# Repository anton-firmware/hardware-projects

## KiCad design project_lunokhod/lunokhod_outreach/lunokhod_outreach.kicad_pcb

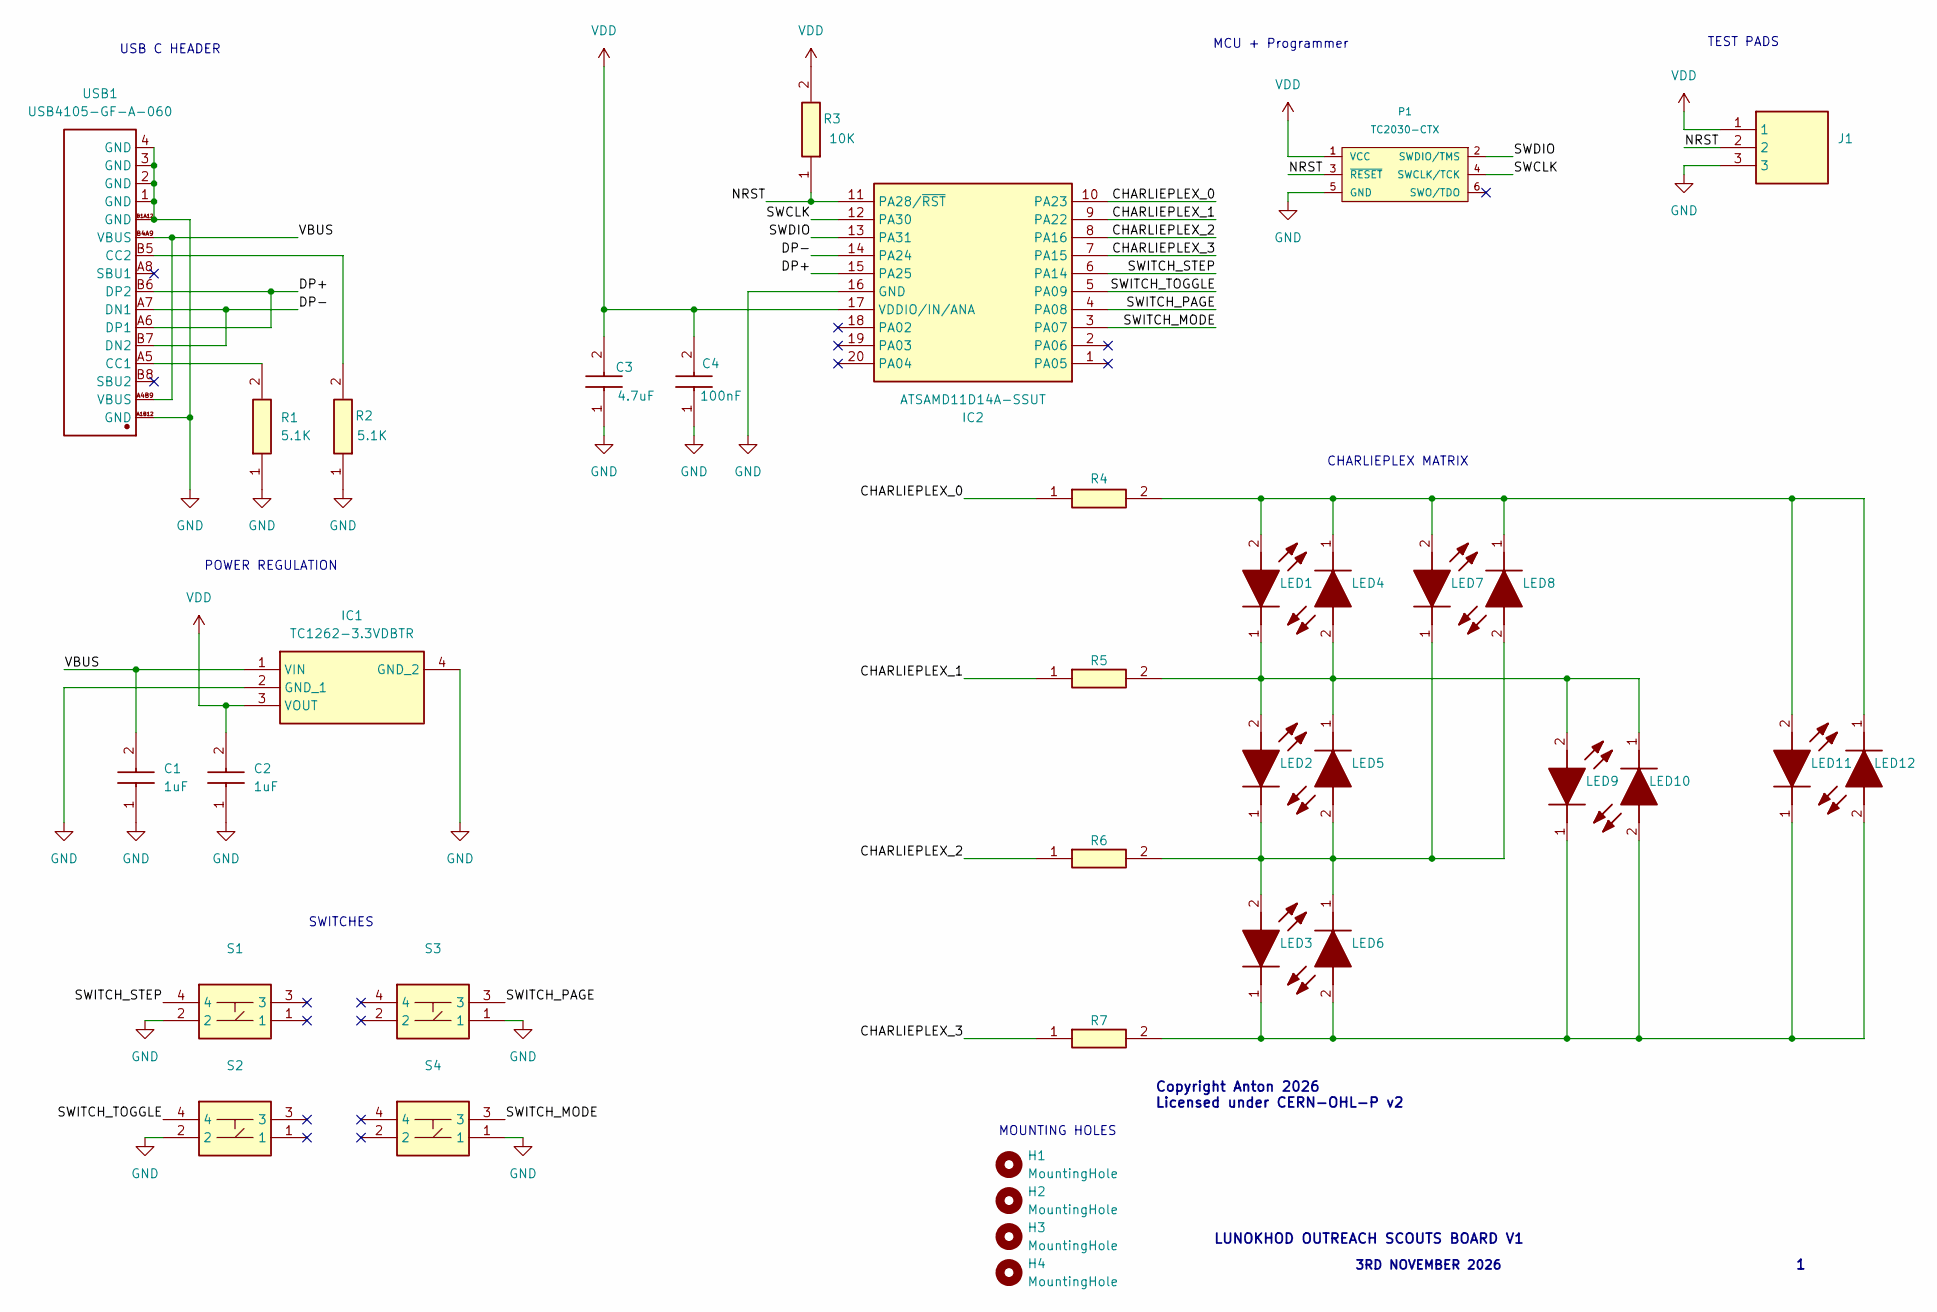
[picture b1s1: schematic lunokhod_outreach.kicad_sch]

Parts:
C1, C2: 1uF; C0603; Manufacturer_Part_Number C0603C101K5RACAUTO7411
C3: 4.7uF; C0603; Manufacturer_Part_Number C0603C101K5RACAUTO7411
C4: 100nF; C0603; Manufacturer_Part_Number C0603C101K5RACAUTO7411
H1, H2, H3, H4: MountingHole; MountingHole_2.5mm
IC1: TC1262-3.3VDBTR; SOT230P700X180-4N; Manufacturer_Part_Number TC1262-3.3VDBTR
IC2: ATSAMD11D14A-SSUT; SOIC127P1032X265-20N; Manufacturer_Part_Number ATSAMD11D14A-SSUT
J1: 0022285034; Manufacturer_Part_Number 0022285034
LED1, LED2, LED3, LED4, LED5, LED6, LED7, LED8, LED9, LED10, LED11, LED12: 703-0100; 7030100; Manufacturer_Part_Number 703-0100
P1: TC2030-CTX; TC2030_SMALL
R1, R2: 5.1K; ERJPC3D9763V; Manufacturer_Part_Number ERJ-PC3B4702V
R3: 10K; ERJPC3D9763V; Manufacturer_Part_Number ERJ-PC3B4702V
R4, R5, R6: LibraryLoader:RESAD3800W75L1600D550; ERJPC3D9763V; Manufacturer_Part_Number MCKNP02WJ0102A19
R7: MCKNP02WJ0102A19; ERJPC3D9763V; Manufacturer_Part_Number MCKNP02WJ0102A19
S1, S2, S3, S4: B3F-1020; B3F1000; Manufacturer_Part_Number B3F-1020
USB1: USB4105-GF-A-060; USB-C-SMD_GT-USB-7010E-1; Manufacturer Part USB4105-GF-A-060

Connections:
/CHARLIEPLEX_0: IC2.10 (PA23), R4.1
/CHARLIEPLEX_1: IC2.9 (PA22), R5.1
/CHARLIEPLEX_2: IC2.8 (PA16), R6.1
/CHARLIEPLEX_3: IC2.7 (PA15), R7.1
/DP+: IC2.15 (PA25), USB1.A6 (DP1), USB1.B6 (DP2)
/DP-: IC2.14 (PA24), USB1.A7 (DN1), USB1.B7 (DN2)
/NRST: IC2.11 (PA28/~RST), J1.2, P1.3 (~RESET), R3.1
/SWCLK: IC2.12 (PA30), P1.4 (SWCLK/TCK)
/SWDIO: IC2.13 (PA31), P1.2 (SWDIO/TMS)
/SWITCH_MODE: IC2.3 (PA07), S4.3
/SWITCH_PAGE: IC2.4 (PA08), S3.3
/SWITCH_STEP: IC2.6 (PA14), S1.4
/SWITCH_TOGGLE: IC2.5 (PA09), S2.4
/VBUS: C1.2, IC1.1 (VIN), USB1.A4B9 (VBUS), USB1.B4A9 (VBUS)
GND: C1.1, C2.1, C3.1, C4.1, IC1.2 (GND_1), IC1.4 (GND_2), IC2.16 (GND), J1.3, P1.5 (GND), R1.1, R2.1, S1.2, S2.2, S3.1, S4.1, USB1.1 (GND), USB1.2 (GND), USB1.3 (GND), USB1.4 (GND), USB1.A1B12 (GND), USB1.B1A12 (GND)
unnamed: LED1.2 (A), LED4.1 (K), LED7.2 (A), LED8.1 (K), LED11.2 (A), LED12.1 (K), R4.2
unnamed: LED1.1 (K), LED2.2 (A), LED4.2 (A), LED5.1 (K), LED9.2 (A), LED10.1 (K), R5.2
unnamed: LED2.1 (K), LED3.2 (A), LED5.2 (A), LED6.1 (K), LED7.1 (K), LED8.2 (A), R6.2
unnamed: LED3.1 (K), LED6.2 (A), LED9.1 (K), LED10.2 (A), LED11.1 (K), LED12.2 (A), R7.2
unnamed: R1.2, USB1.A5 (CC1)
unnamed: R2.2, USB1.B5 (CC2)
VDD: C2.2, C3.2, C4.2, IC1.3 (VOUT), IC2.17 (VDDIO/IN/ANA), J1.1, P1.1 (VCC), R3.2

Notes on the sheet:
SWITCHES
LUNOKHOD OUTREACH SCOUTS BOARD V1
POWER REGULATION
CHARLIEPLEX MATRIX
TEST PADS
Copyright Anton 2026 Licensed under CERN-OHL-P v2
USB C HEADER
MCU + Programmer
MOUNTING HOLES
3RD NOVEMBER 2026

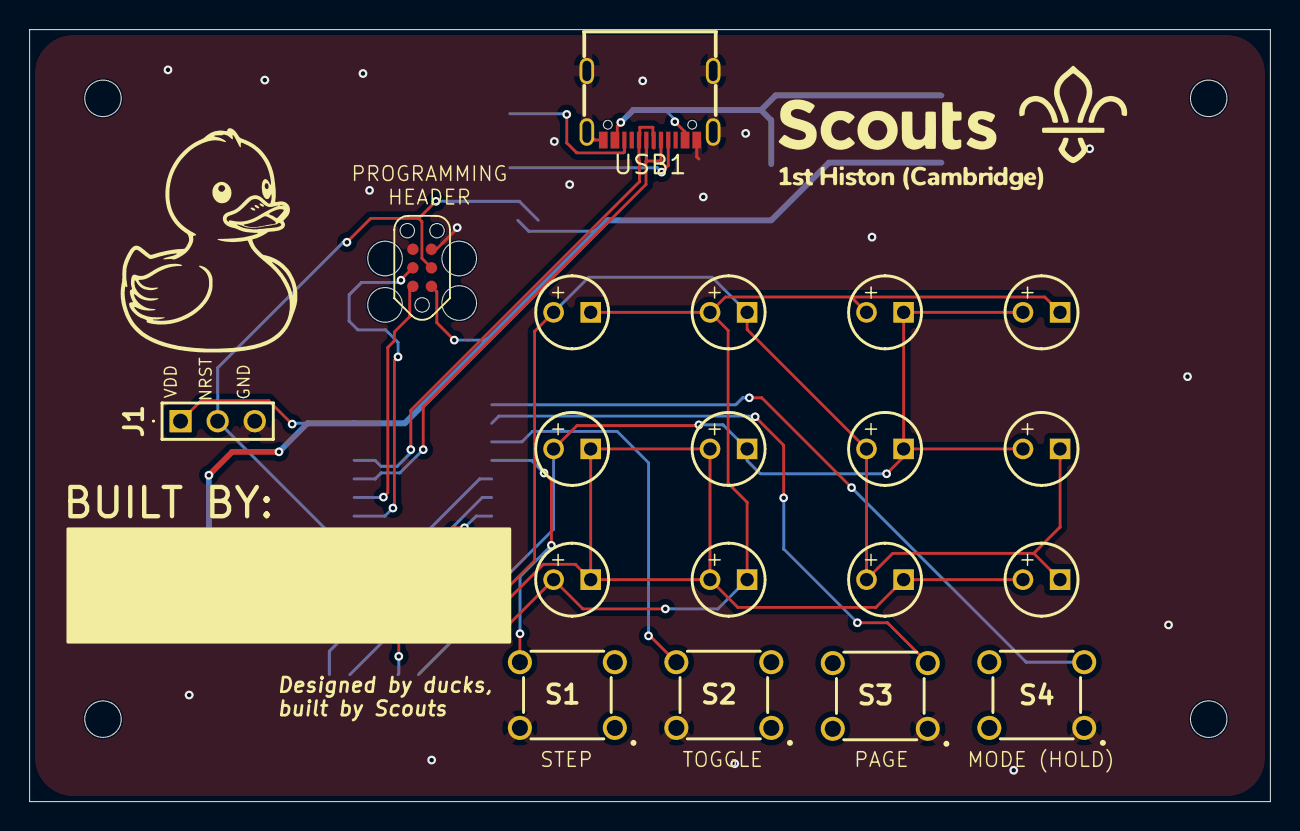
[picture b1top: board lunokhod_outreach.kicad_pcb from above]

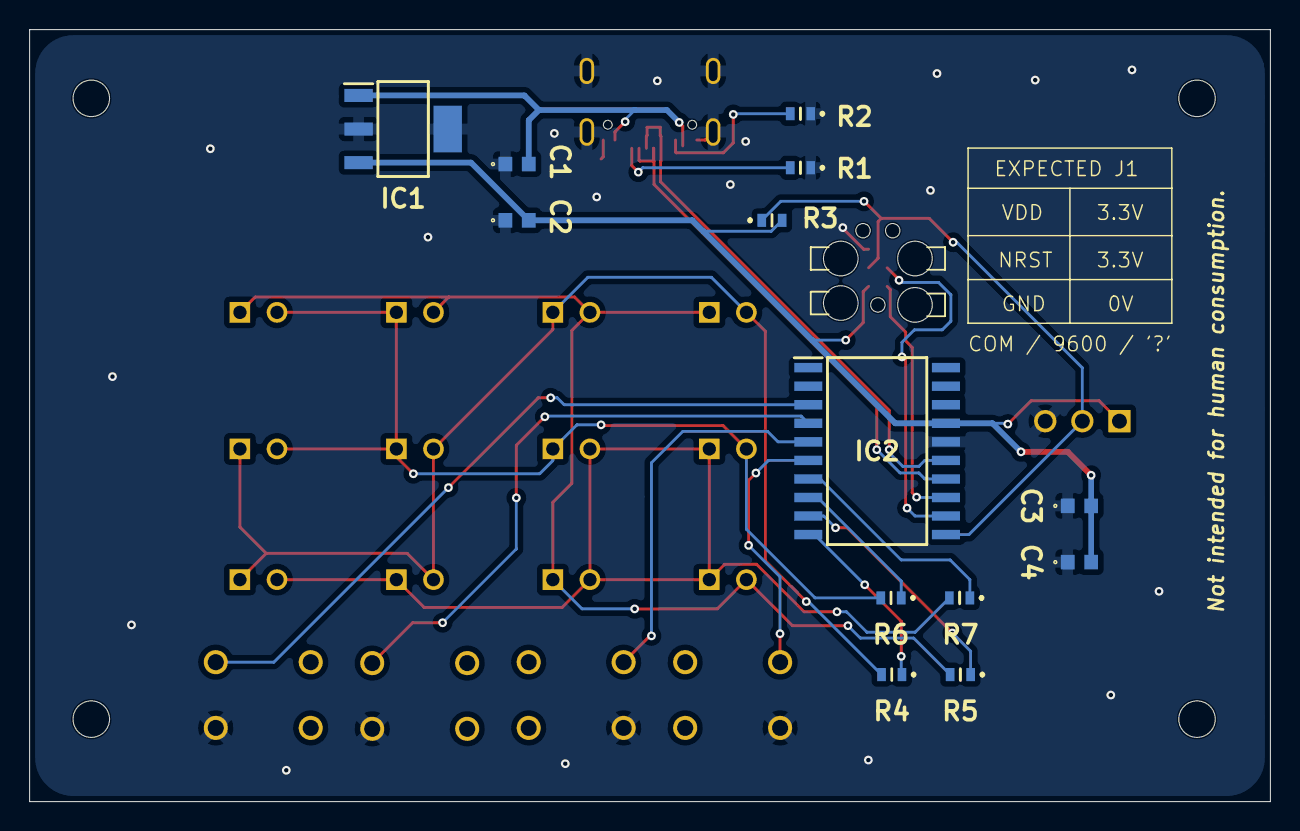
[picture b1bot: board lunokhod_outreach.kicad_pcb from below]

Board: 2 copper layers, 84.9 x 52.9 mm, 36 parts (13 on the bottom side), 22 nets.

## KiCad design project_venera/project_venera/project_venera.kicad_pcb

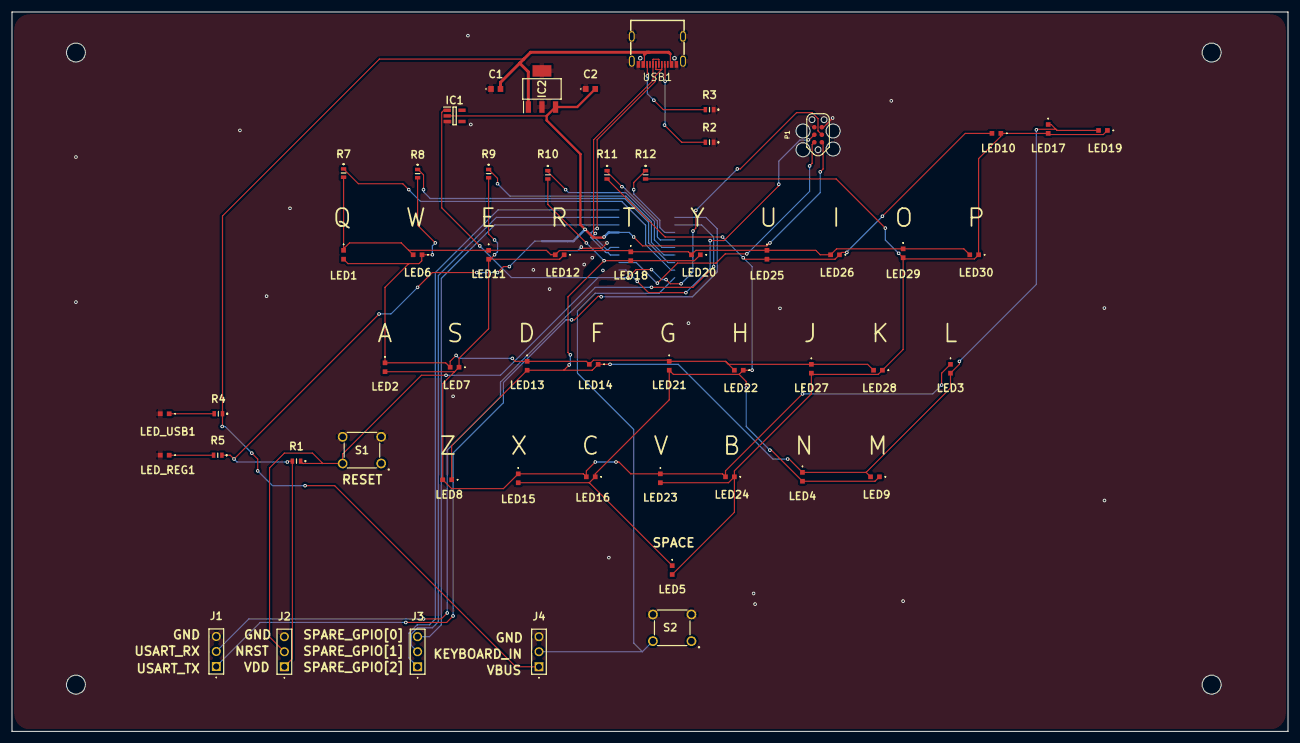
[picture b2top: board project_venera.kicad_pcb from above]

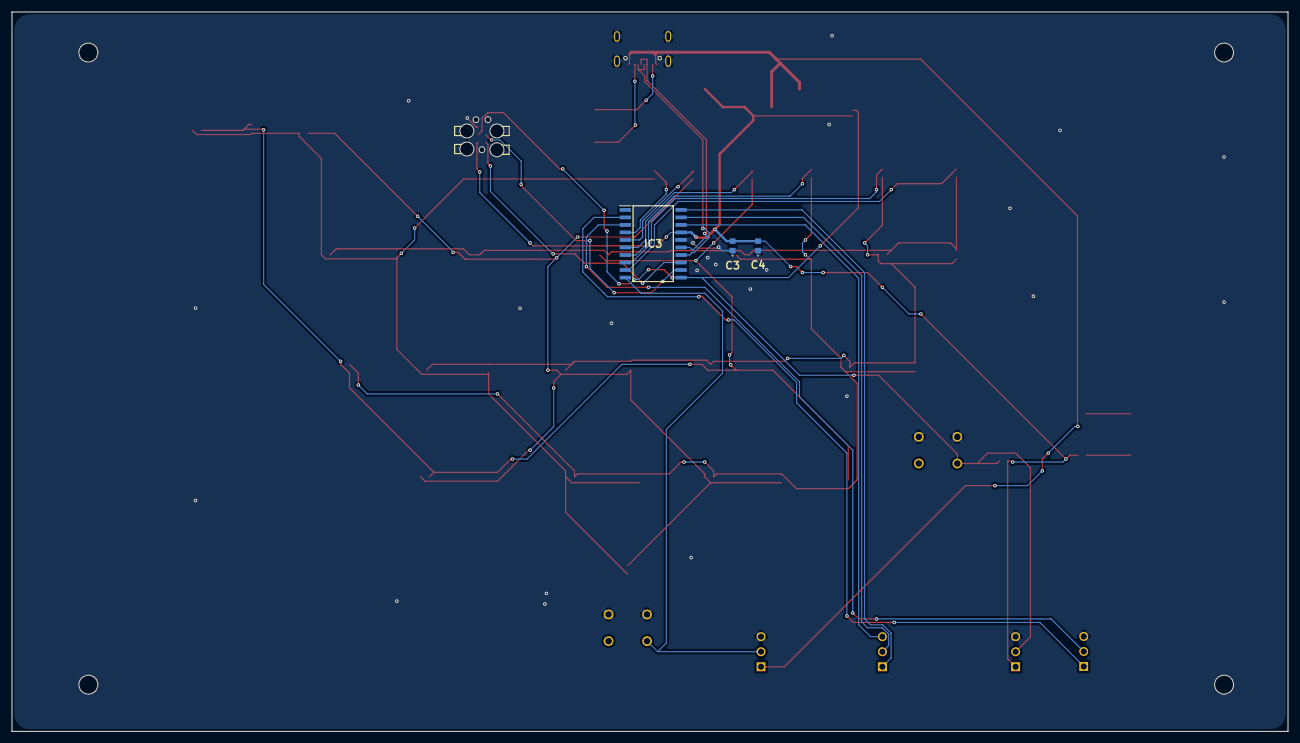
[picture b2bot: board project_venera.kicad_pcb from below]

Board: 2 copper layers, 215.5 x 121.5 mm, 58 parts (3 on the bottom side), 30 nets.

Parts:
C1, C2: 1uF; C0603
C3: 100nF; C0603
C4: 4.7uF; C0603
IC1: NCV303LSN11T1G; SOT95P275X110-5N
IC2: TC1262-3.3VDBTR; SOT230P700X180-4N
IC3: ATSAMD11D14A-SSUT; SOIC127P1032X265-20N
J1, J2, J3, J4: 0022285034
LED1, LED2, LED3, LED4, LED5, LED6, LED7, LED8, LED9, LED10, LED11, LED12, LED13, LED14, LED15, LED16, LED17, LED18, LED19, LED20, LED21, LED22, LED23, LED24, LED25, LED26, LED27, LED28, LED29, LED30: SM0603SRC
LED_REG1: SM0603SRC
LED_USB1: SM0603SRC
P1: TC2030-CTX; TC2030_SMALL
R1: 10K; ERJPC3D9763V
R2, R3: 5.1K; ERJPC3D9763V
R4, R5, R7, R8, R9, R10, R11, R12: TBD; ERJPC3D9763V
S1, S2: B3F-1020; B3F1000
USB1: USB4105-GF-A-060; USB-C-SMD_GT-USB-7010E-1

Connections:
/DP+: IC3.15 (PA25), USB1.A6 (DP1), USB1.B6 (DP2)
/DP-: IC3.14 (PA24), USB1.A7 (DN1), USB1.B7 (DN2)
/KEYBOARD_IN: IC3.10 (PA23), J4.2, S2.2
/LED Array/CHARLIEPLEXING_0: IC3.9 (PA22), R7.1
/LED Array/CHARLIEPLEXING_1: IC3.8 (PA16), R8.1
/LED Array/CHARLIEPLEXING_2: IC3.7 (PA15), R9.1
/LED Array/CHARLIEPLEXING_3: IC3.6 (PA14), R10.1
/LED Array/CHARLIEPLEXING_4: IC3.5 (PA09), R11.1
/LED Array/CHARLIEPLEXING_5: IC3.4 (PA08), R12.1
/NRST: IC1.1 (RESET_OUTPUT), IC3.11 (PA28/~RST), J2.2, P1.3 (~RESET), R1.1, S1.2
/SPARE_GPIO[0]: IC3.18 (PA02), J3.3
/SPARE_GPIO[1]: IC3.19 (PA03), J3.2
/SPARE_GPIO[2]: IC3.20 (PA04), J3.1
/SWCLK: IC3.12 (PA30), P1.4 (SWCLK/TCK)
/SWDIO: IC3.13 (PA31), P1.2 (SWDIO/TMS)
/USART_RX: IC3.3 (PA07), J1.2
/USART_TX: IC3.2 (PA06), J1.1
/VBUS: C1.2, IC2.1 (VIN), J4.1, R4.1, USB1.A4B9 (VBUS), USB1.B4A9 (VBUS)
GND: C1.1, C2.1, C3.1, C4.1, IC1.3 (GROUND), IC2.2 (GND_1), IC2.4 (GND_2), IC3.16 (GND), J1.3, J2.3, J4.3, LED_REG1.2 (K), LED_USB1.2 (K), P1.5 (GND), R2.1, R3.1, S1.3, S1.4, S2.3, S2.4, USB1.1 (GND), USB1.2 (GND), USB1.3 (GND), USB1.4 (GND), USB1.A1B12 (GND), USB1.B1A12 (GND)
unnamed: LED1.1 (A), LED6.2 (K), LED11.1 (A), LED12.2 (K), LED18.1 (A), LED20.2 (K), LED25.1 (A), LED26.2 (K), LED29.1 (A), LED30.2 (K), R7.2
unnamed: LED1.2 (K), LED2.1 (A), LED6.1 (A), LED7.2 (K), LED13.1 (A), LED14.2 (K), LED21.1 (A), LED22.2 (K), LED27.1 (A), LED28.2 (K), R8.2
unnamed: LED5.2 (K), LED10.1 (A), LED17.2 (K), LED19.1 (A), LED23.2 (K), LED24.1 (A), LED27.2 (K), LED28.1 (A), LED29.2 (K), LED30.1 (A), R12.2
unnamed: LED4.2 (K), LED5.1 (A), LED9.1 (A), LED10.2 (K), LED15.2 (K), LED16.1 (A), LED21.2 (K), LED22.1 (A), LED25.2 (K), LED26.1 (A), R11.2
unnamed: LED2.2 (K), LED3.1 (A), LED7.1 (A), LED8.2 (K), LED11.2 (K), LED12.1 (A), LED15.1 (A), LED16.2 (K), LED23.1 (A), LED24.2 (K), R9.2
unnamed: LED3.2 (K), LED4.1 (A), LED8.1 (A), LED9.2 (K), LED13.2 (K), LED14.1 (A), LED17.1 (A), LED18.2 (K), LED19.2 (K), LED20.1 (A), R10.2
unnamed: LED_REG1.1 (A), R5.2
unnamed: LED_USB1.1 (A), R4.2
unnamed: R2.2, USB1.A5 (CC1)
unnamed: R3.2, USB1.B5 (CC2)
VDD: C2.2, C3.2, C4.2, IC1.2 (INPUT), IC2.3 (VOUT), IC3.17 (VDDIO/IN/ANA), J2.1, P1.1 (VCC), R1.2, R5.1

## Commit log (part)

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2026-06-14 initial upload, gitignore
2026-06-14 update gitignore
2026-06-14 upload wip hw files
2026-06-17 add charlieplexing array sheet
2026-06-17 update main schematic page, add buttons, gpio pins
